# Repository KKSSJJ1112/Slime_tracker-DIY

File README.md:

# UNCZ_Slime_tracker

[English](#english) | [한국어](#한국어)

---

## English

### Overview
Custom SlimeVR tracker.

### Specifications
| Item | Description |
|------|-------------|
| MCU | ESP32-C3 Super Mini |
| IMU | SlimeVR Mumo Breakout Module V1 (ICM-45686 + QMC6309) |
| Battery | 1100mAh Li-Po |
| PCB Size | ~80mm x 30mm |

### Features
- **Optimized Power Circuit**: Minimized ripple and noise compared
- **Compact Form Factor**: Streamlined 2-layer PCB design
- **Production Ready**: Includes JLCPCB manufacturing files

### Repository Structure
```
├── 3D/                    # 3D model files (case, mount, etc.)
├── Datasheets/            # Component datasheets
├── KiCad/                 # KiCad project files
│   ├── *.kicad_pcb
│   ├── *.kicad_sch
│   └── *.kicad_pro
└── Production/            # Manufacturing files
    ├── BOM.csv            # Bill of Materials (JLCPCB format)
    ├── PartList.csv       # Component list
    └── Positions.csv      # Pick and place file
```

### Manufacturing
Production files are optimized for JLCPCB:
1. Upload Gerber files from `Production/` folder
2. Use provided BOM and position files for SMT assembly

### Power Circuit Comparison
<!-- Add your oscilloscope comparison images here -->

77mv -> 20mv

From bottom to top: immediately after boost converter, after LC filter, and before final IMU power supply.

### License
- Hardware (PCB, Schematics, 3D files): [MIT License](LICENSE)
- Documentation: [CC BY-SA 4.0](https://creativecommons.org/licenses/by-sa/4.0/)

### Revision History
- **Rev02** (Current): Power circuit, Charging circuit changed
- **Rev01**: Initial design

---

## 한국어

### 개요
커스텀 SlimeVR 트래커입니다.

### 사양
| 항목 | 내용 |
|------|------|
| MCU | ESP32-C3 Super Mini |
| IMU | SlimeVR Mumo Breakout Module V1 (ICM-45686 + QMC6309) |
| 배터리 | 1100mAh Li-Po |
| PCB 크기 | 약 80mm x 30mm |

### 특징
- **전원부 최적화**: 리플 및 노이즈 최소화
- **컴팩트 설계**: 2레이어 PCB 기반 간결한 설계
- **양산 대응**: JLCPCB 제조 파일 포함

### 저장소 구조
```
├── 3D/                    # 3D 모델 파일 (케이스, 마운트 등)
├── Datasheets/            # 부품 데이터시트
├── KiCad/                 # KiCad 프로젝트 파일
│   ├── *.kicad_pcb
│   ├── *.kicad_sch
│   └── *.kicad_pro
└── Production/            # 제조용 파일
    ├── BOM.csv            # 부품 목록 (JLCPCB 형식)
    ├── PartList.csv       # 파트 리스트
    └── Positions.csv      # 부품 배치 파일
```

### 제조 방법
JLCPCB 기준 제조 파일 제공:
1. `Production/` 폴더의 거버 파일 업로드
2. 제공된 BOM 및 위치 파일로 SMT 조립 주문

#### 전원부 비교
<!-- 오실로스코프 비교 이미지 추가 예정 -->

77mv -> 20mv 

맨 아래부터 승압 직후, LC필터 이후, 최종 imu공급 직전

### 라이선스
- Hardware (PCB, Schematics, 3D files): [MIT License](LICENSE)
- Documentation: [CC BY-SA 4.0](https://creativecommons.org/licenses/by-sa/4.0/)

### 변경 이력
- **Rev02** (현재): 전원부, 충전부 수정
- **Rev01**: 최초 설계

---

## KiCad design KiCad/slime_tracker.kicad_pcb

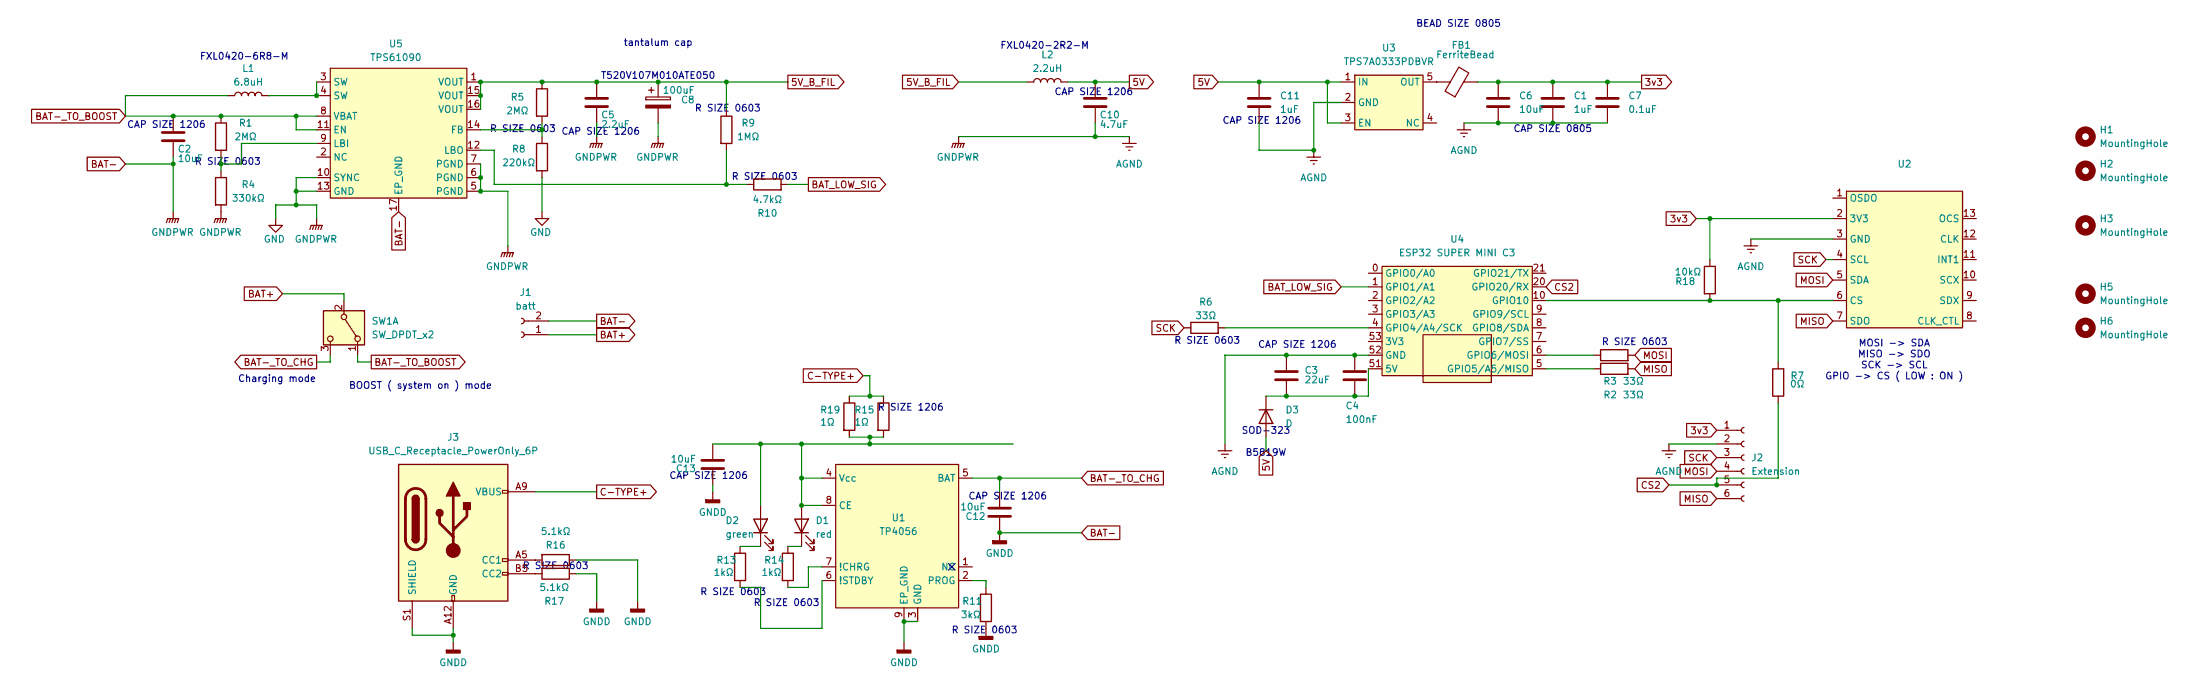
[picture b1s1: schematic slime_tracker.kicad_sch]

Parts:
C1: 1uF; C_0805_2012Metric
C2, C12, C13: 10uF; C_1206_3216Metric
C3: 22uF; C_1206_3216Metric
C4: 100nF; C_1206_3216Metric
C5: 2.2uF; C_1206_3216Metric
C6: 10uF; C_0805_2012Metric
C7: 0.1uF; C_0805_2012Metric
C8: 100uF; CP_EIA-7343-20_Kemet-V
C10: 4.7uF; C_1206_3216Metric
C11: 1uF; C_1206_3216Metric
D1: red; LED_0805_2012Metric
D2: green; LED_0805_2012Metric
D3: D; D_SOD-123
FB1: FerriteBead; R_0805_2012Metric
H1, H2: MountingHole; MountingHole_3.2mm_M3
H3, H5, H6: MountingHole; ToolingHole_1.152mm
J1: batt; JST_PH_S2B-PH-K_1x02_P2.00mm_Horizontal
J2: Extension; JST_PH_S6B-PH-K_1x06_P2.00mm_Horizontal
J3: USB_C_Receptacle_PowerOnly_6P; USB_C_Receptacle_GCT_USB4135-GF-A_6P_TopMnt_Horizontal
L1: 6.8uH; FXL0420
L2: 2.2uH; FXL0420
R1, R5: 2MΩ; R_0603_1608Metric
R2, R3, R6: 33Ω; R_0603_1608Metric
R4: 330kΩ; R_0603_1608Metric
R7: 0Ω; R_0603_1608Metric
R8: 220kΩ; R_0603_1608Metric
R9: 1MΩ; R_0603_1608Metric
R10: 4.7kΩ; R_0603_1608Metric
R11: 3kΩ; R_0603_1608Metric
R13, R14: 1kΩ; R_0603_1608Metric
R15, R19: 1Ω; R_1206_3216Metric
R16, R17: 5.1kΩ; R_0603_1608Metric
R18: 10kΩ; R_0603_1608Metric
SW1: SW_DPDT_x2; SW_Slide_SPDT_Angled_CK_OS102011MA1Q
U1: TP4056; TP4056_ESOP8
U2: Slime_IMU_mumo
U3: TPS7A0333PDBVR; SOT-23-5
U4: ESP32 SUPER MINI C3; esp32
U5: TPS61090; QFN-16-1EP_4x4mm_P0.65mm_EP2.7x2.7mm_PullBack_ThermalVias

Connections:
3v3: C1.1, C6.1, C7.1, FB1.2, J2.1, R18.1, U2.2 (3V3)
5V: C10.2, C11.1, D3.2 (A), L2.2, U3.1 (IN), U3.3 (EN)
5V_B_FIL: C5.2, C8.1, L2.1, R5.1, R9.1, U5.1 (VOUT), U5.15 (VOUT), U5.16 (VOUT)
BAT+: J1.1, SW1.2 (B)
BAT-: C1.2, C2.1, C3.2, C4.2, C5.1, C6.2, C7.2, C8.2, C10.1, C11.2, C12.2, C13.2, J1.2, J2.2, J3.A12 (GND), J3.B12 (GND), J3.S1 (SHIELD), R4.2, R8.2, R11.2, R16.1, R17.1, U1.3 (GND), U1.9 (EP_GND), U2.3 (GND), U3.2 (GND), U4.52 (GND), U5.5 (PGND), U5.6 (PGND), U5.7 (PGND), U5.10 (SYNC), U5.13 (GND), U5.17 (EP_GND)
BAT-_TO_BOOST: C2.2, L1.1, R1.1, SW1.1 (A), U5.8 (VBAT), U5.11 (EN)
BAT-_TO_CHG: C12.1, SW1.3 (C), U1.5 (BAT)
BAT_LOW_SIG: R10.2, U4.1 (GPIO1/A1)
C-TYPE+: J3.A9 (VBUS), J3.B9 (VBUS), R15.1, R19.1
CS2: J2.5, R7.1, U4.20 (GPIO20/RX)
MISO: J2.6, R2.2, U2.7 (SDO)
MOSI: J2.4, R3.2, U2.5 (SDA)
unnamed: C13.1, D1.2 (A), D2.2 (A), R15.2, R19.2, U1.4 (Vcc), U1.8 (CE)
unnamed: D1.1 (K), R14.1
unnamed: D2.1 (K), R13.1
unnamed: C3.1, C4.1, D3.1 (K), U4.51 (5V)
unnamed: J3.A5 (CC1), R16.2
unnamed: J3.B5 (CC2), R17.2
unnamed: L1.2, U5.3 (SW), U5.4 (SW)
unnamed: R14.2, U1.7 (!CHRG)
unnamed: R13.2, U1.6 (!STDBY)
unnamed: R11.1, U1.2 (PROG)
unnamed: R7.2, R18.2, U2.6 (CS), U4.10 (GPIO10)
unnamed: FB1.1, U3.5 (OUT)
unnamed: R6.2, U4.4 (GPIO4/A4/SCK)
unnamed: R2.1, U4.5 (GPIO5/A5/MISO)
unnamed: R3.1, U4.6 (GPIO6/MOSI)
unnamed: R5.2, R8.1, U5.14 (FB)
unnamed: R1.2, R4.1, U5.9 (LBI)
unnamed: R9.2, R10.1, U5.12 (LBO)
SCK: J2.3, R6.1, U2.4 (SCL)

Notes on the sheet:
R SIZE 0603
CAP SIZE 1206
R SIZE 1206
BOOST ( system on ) mode
FXL0420-2R2-M
CAP SIZE 0805
tantalum cap T520V107M010ATE050
FXL0420-6R8-M
SOD-323 B5819W
Charging mode
BEAD SIZE 0805
MOSI -> SDA MISO -> SDO SCK -> SCL GPIO -> CS ( LOW : ON )

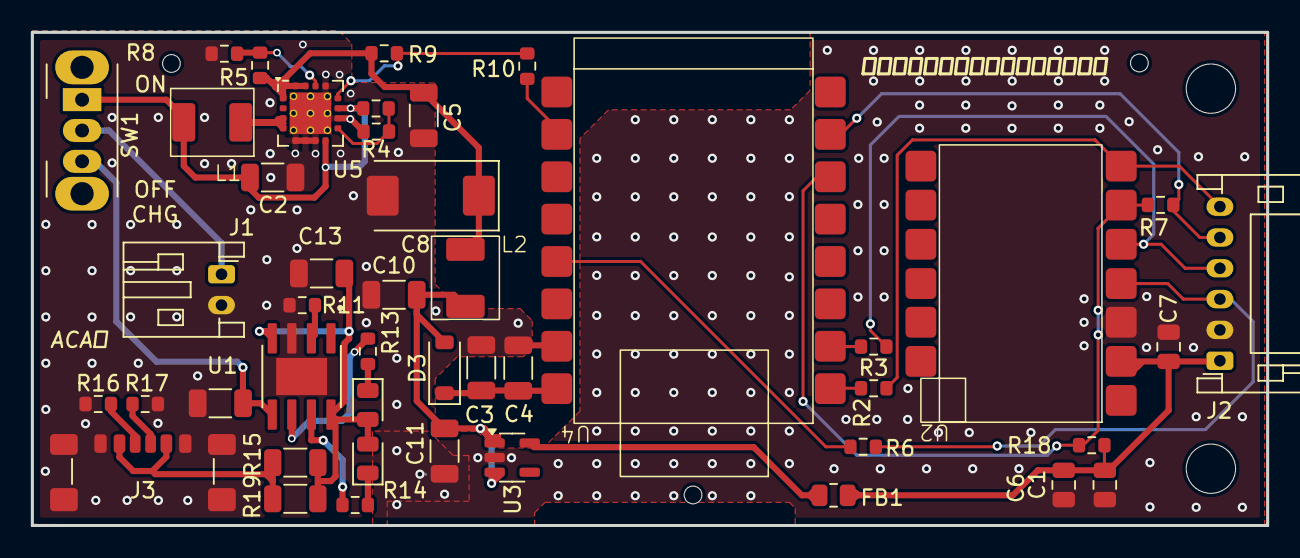
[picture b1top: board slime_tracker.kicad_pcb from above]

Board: 2 copper layers, 80.2 x 32.0 mm, 50 parts (0 on the bottom side), 31 nets.

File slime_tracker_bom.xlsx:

Reference | Qty | Value | DNP | Exclude from BOM | Exclude from Board | Footprint | JLC PART # | Datasheet
C1 | 1 | 1uF |  |  |  | Capacitor_SMD:C_0805_2012Metric | C1712 | ~
C2,C12,C13 | 3 | 10uF |  |  |  | Capacitor_SMD:C_1206_3216Metric | C70462 | ~
C3 | 1 | 22uF |  |  |  | Capacitor_SMD:C_1206_3216Metric | C5252682 | ~
C4 | 1 | 100nF |  |  |  | Capacitor_SMD:C_1206_3216Metric | C82601 | ~
C5 | 1 | 2.2uF |  |  |  | Capacitor_SMD:C_1206_3216Metric | C577211 | ~
C6 | 1 | 10uF |  |  |  | Capacitor_SMD:C_0805_2012Metric | C6119932 | ~
C7 | 1 | 0.1uF |  |  |  | Capacitor_SMD:C_0805_2012Metric | C519981 | ~
C8 | 1 | 100uF |  |  |  | Capacitor_Tantalum_SMD:CASE-B-3528-21(mm) kemet | C600583 | ~
C9,C10 | 2 | 1.5uF |  |  |  | Capacitor_SMD:C_1206_3216Metric | C282844 | ~
C11 | 1 | 1uF |  |  |  | Capacitor_SMD:C_1206_3216Metric | C107184 | ~
D1 | 1 | red |  |  |  | LED_SMD:LED_1206_3216Metric | C84270 | ~
D2 | 1 | green |  |  |  | LED_SMD:LED_1206_3216Metric | C14641 | ~
D3 | 1 | D |  |  |  | Diode_SMD:D_SOD-323 | C22624
FB1 | 1 | FerriteBead |  |  |  | Resistor_SMD:R_0805_2012Metric | C67451 | ~
H1,H2 | 2 | MountingHole | DNP | ",MountingHole:MountingHole_3.2mm_M3" | ~ | ~ | ~
H3,H5,H6 | 3 | MountingHole | DNP | MountingHole:ToolingHole_1.152mm | ~ | ~ | ~
J1 | 1 | batt | DNP | ",Connector_JST:JST_PH_S2B-PH-K_1x02_P2.00mm_Horizontal" | ~ | ~ | ~
J3 | 1 | USB_C_Receptacle_PowerOnly_6P |  |  |  | Connector_USB:USB_C_Receptacle_GCT_USB4135-GF-A_6P_TopMnt_Horizontal | C5438410 | https://www.usb.org/sites/default/files/documents/usb_type-c.zip
L1 | 1 | 6.8uH |  |  |  | slime:FXL0420 | C177241 | ~
L2 | 1 | 2.2uH |  |  |  | slime:FXL0420 | C167206 | ~
R1,R5 | 2 | 1.8MOhm |  |  |  | Resistor_SMD:R_0603_1608Metric | C13318 | ~
R2,R3,R6,R7 | 4 | 33Ohm |  |  |  | Resistor_SMD:R_0603_1608Metric | C23140 | ~
R4 | 1 | 390kOhm |  |  |  | Resistor_SMD:R_0603_1608Metric | C23150 | ~
R8 | 1 | 200kOhm |  |  |  | Resistor_SMD:R_0603_1608Metric | C25811 | ~
R9 | 1 | 1MOhm |  |  |  | Resistor_SMD:R_0603_1608Metric | C22935 | ~
R10 | 1 | 4.7kOhm |  |  |  | Resistor_SMD:R_0603_1608Metric | C23162 | ~
R11 | 1 | 3kOhm |  |  |  | Resistor_SMD:R_0603_1608Metric | C4211 | ~
R12 | 1 | 10kOhm |  |  |  | Resistor_SMD:R_0603_1608Metric | C25804 | ~
R13,R14 | 2 | 1kOhm |  |  |  | Resistor_SMD:R_0603_1608Metric | C21190 | ~
R15 | 1 | 0.4Ohm |  |  |  | Resistor_SMD:R_2010_5025Metric | C2999599 | ~
R16,R17 | 2 | 5.1kOhm |  |  |  | Resistor_SMD:R_0603_1608Metric | C23186 | ~
SW1 | 1 | SW_DPDT_x2 | DNP | Button_Switch_THT:SW_Slide_SPDT_Angled_CK_OS102011MA1Q" | ~ | ~ | ~
TP1 | 1 | SCL |  |  |  | TestPoint:TestPoint_Pad_2.5x2.5mm | ~ | ~
TP2 | 1 | SDA |  |  |  | TestPoint:TestPoint_Pad_2.5x2.5mm | ~ | ~
TP3 | 1 | 3.3v |  |  |  | TestPoint:TestPoint_Pad_2.5x2.5mm | ~ | ~
TP4 | 1 | GND |  |  |  | TestPoint:TestPoint_Pad_2.5x2.5mm | ~ | ~
TP5 | 1 | INT2 |  |  |  | TestPoint:TestPoint_Pad_2.5x2.5mm | ~ | ~
U1 | 1 | TP4056 |  |  |  | slime:TP4056_ESOP8 | C725790
U2 | 1 | ~ | DNP | "slime:Slime_IMU_mumo" | ~ | ~ | ~
U3 | 1 | TPS7A0333PDBVR |  |  |  | Package_TO_SOT_SMD:SOT-23-5 | C3749797
U4 | 1 | ESP32 SUPER MINI C3 | DNP | ",slime:esp32" | ~ | ~ | ~
U5 | 1 | TPS61090 |  |  |  | Package_DFN_QFN:QFN-16-1EP_4x4mm_P0.65mm_EP2.7x2.7mm_PullBack_ThermalVias | C206167

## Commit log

2025-11-13 imu 풋프린트 필요
2025-11-17 artwork_almost
    artwork_almost
2025-11-18 c-type_rollback
2025-11-18 FROM HOME
2025-11-19 polanized cap
2025-12-16 3D file
    3D file
2025-12-16 Rename base final.stl to 3D/base final.stl
2025-12-16 Rename KiCad/.t. to KiCad/slime.pretty/t.
2025-12-16 Rev_02
2025-12-16 for JLCPCB
2025-12-16 Revise README for power circuit and licensing details
    Updated the README with power circuit comparison details, license information, and revision history.
2025-12-16 Change copyright name in MIT License
    Updated copyright holder name in MIT License.
2025-12-31 subTracker added
2025-12-31 Create aa
2025-12-31 Create vr
2025-12-31 firmwareFile
2026-01-16 IC2, SPI explain added
    and N.C R added
